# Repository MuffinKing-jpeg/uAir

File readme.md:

# uAir

Small air monitor with OLED screen

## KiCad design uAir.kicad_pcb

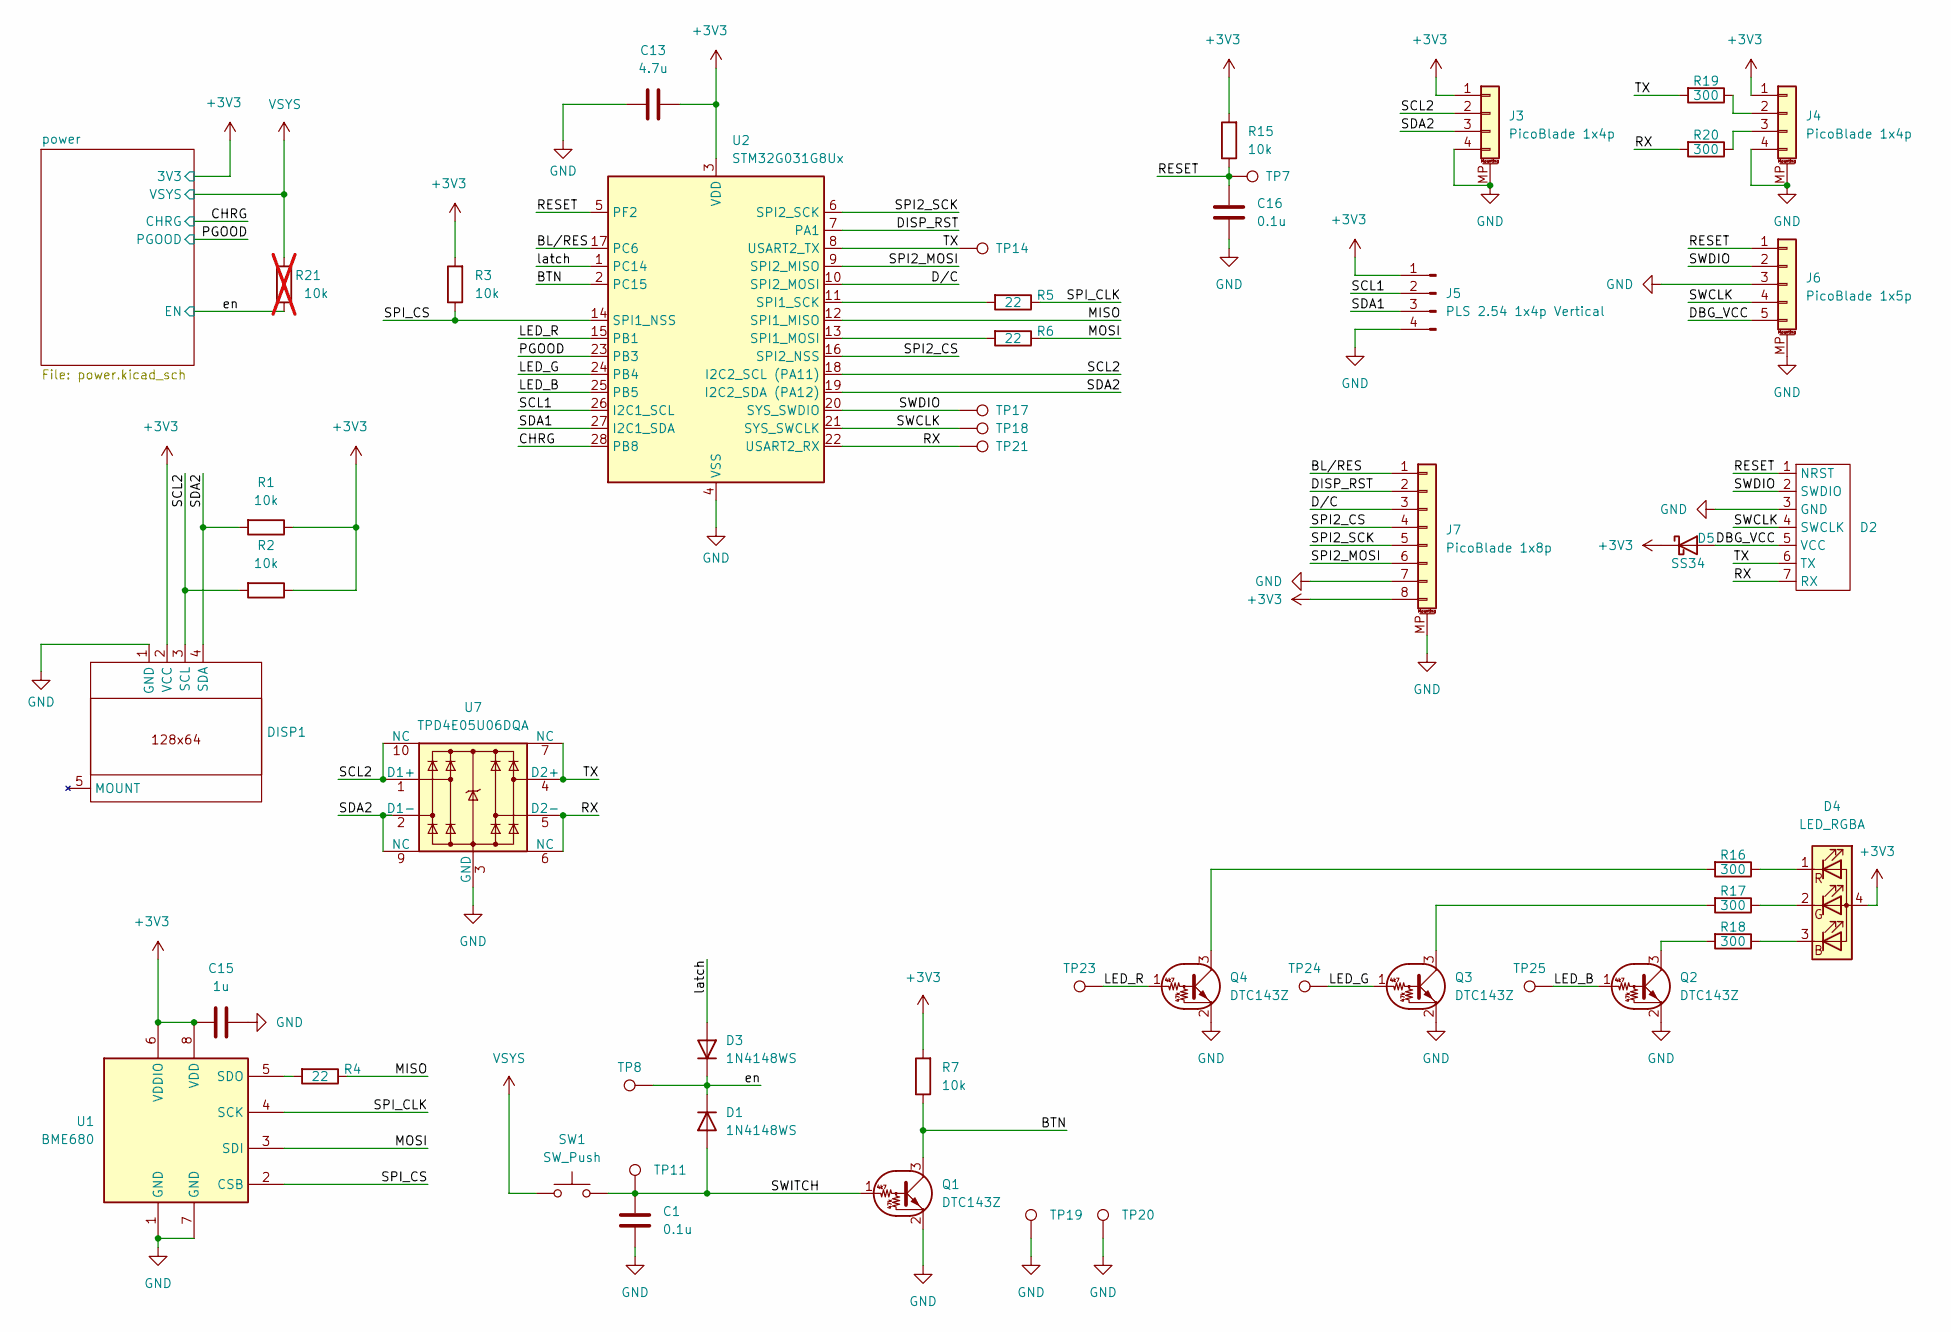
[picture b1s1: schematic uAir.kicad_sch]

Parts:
C1, C16: 0.1u; C_0402_1005Metric
C13: 4.7u; C_0603_1608Metric
C15: 1u; C_0603_1608Metric
D1, D3: 1N4148WS; D_SOD-323; LCSC C6423741
D2: DBG-CLIP-7_pad
D4: LED_RGBA; LED_LiteOn_LTST-C19HE1WT; LCSC C125110
D5: SS34; D_SMA
DISP1: OLED_Module_I2C_WeAct
J3, J4: PicoBlade 1x4p; Molex_PicoBlade_53261-0471_1x04-1MP_P1.25mm_Horizontal
J5: PLS 2.54 1x4p Vertical; PinHeader_1x04_P2.54mm_Vertical
J6: PicoBlade 1x5p; Molex_PicoBlade_53261-0571_1x05-1MP_P1.25mm_Horizontal
J7: PicoBlade 1x8p; Molex_PicoBlade_53261-0871_1x08-1MP_P1.25mm_Horizontal
Q1: DTC143Z; SOT-523; LCSC C2828442
Q2, Q3, Q4: DTC143Z; SC-59; LCSC C2828442
R1, R2, R3, R7, R15: 10k; R_0603_1608Metric
R4, R5, R6: 22; R_0603_1608Metric
R16, R17, R18, R19, R20: 300; R_0603_1608Metric
R21: 10k; R_0603_1608Metric; not fitted
SW1: SW_Push; SW_Kailh_Choc_V1V2_Led
TP7: nRESET; TestPoint_THTPad_D1.0mm_Drill0.5mm
TP8: EN; TestPoint_THTPad_D1.0mm_Drill0.5mm
TP11: SWITCH; TestPoint_Pad_D1.0mm
TP14: TX; TestPoint_THTPad_D1.0mm_Drill0.5mm
TP17: SWDIO; TestPoint_THTPad_D1.0mm_Drill0.5mm
TP18: SWCLK; TestPoint_THTPad_D1.0mm_Drill0.5mm
TP19, TP20: GND; TestPoint_THTPad_D1.0mm_Drill0.5mm
TP21: RX; TestPoint_THTPad_D1.0mm_Drill0.5mm
TP23: LED_R; TestPoint_THTPad_D1.0mm_Drill0.5mm
TP24: LED_G; TestPoint_THTPad_D1.0mm_Drill0.5mm
TP25: LED_B; TestPoint_THTPad_D1.0mm_Drill0.5mm
U1: BME680; Bosch_LGA-8_3x3mm_P0.8mm_ClockwisePinNumbering
U2: STM32G031G8Ux; QFN-28_4x4mm_P0.5mm
U7: TPD4E05U06DQA; USON-10_2.5x1.0mm_P0.5mm

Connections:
+3V3: C13.2, C15.1, D4.4 (A), D5.1 (K), DISP1.2 (VCC), J3.1, J4.1, J5.1, J7.8, R1.1, R2.1, R3.2, R7.2, R15.2, U1.6 (VDDIO), U1.8 (VDD), U2.3 (VDD); also elsewhere on the board
/BL/RES: J7.1, U2.17 (PC6)
/BTN: Q1.3 (C), R7.1, U2.2 (PC15)
/CHRG: U2.28 (PB8); also elsewhere on the board
/DBG_VCC: D2.5 (VCC), D5.2 (A), J6.5
/DISP_RST: J7.2, U2.7 (PA1)
/D/C: J7.3, U2.10 (SPI2_MOSI)
/LED_B: Q2.1 (B), TP25.1 (1_1), U2.25 (PB5)
/LED_G: Q3.1 (B), TP24.1 (1_1), U2.24 (PB4)
/LED_R: Q4.1 (B), TP23.1 (1_1), U2.15 (PB1)
/MISO: R4.1, U2.12 (SPI1_MISO)
/MOSI: R6.1, U1.3 (SDI)
/PGOOD: U2.23 (PB3); also elsewhere on the board
/RESET: C16.1, D2.1 (NRST), J6.1, R15.1, TP7.1 (1_1), U2.5 (PF2)
/RX: D2.7 (RX), R20.2, TP21.1 (1_1), U2.22 (USART2_RX), U7.5 (D2-), U7.6 (NC)
/SCL1: J5.2, U2.26 (I2C1_SCL)
/SCL2: DISP1.3 (SCL), J3.2, R2.2, U2.18 (I2C2_SCL (PA11)), U7.1 (D1+), U7.10 (NC)
/SDA1: J5.3, U2.27 (I2C1_SDA)
/SDA2: DISP1.4 (SDA), J3.3, R1.2, U2.19 (I2C2_SDA (PA12)), U7.2 (D1-), U7.9 (NC)
/SPI2_CS: J7.4, U2.16 (SPI2_NSS)
/SPI2_MOSI: J7.6, U2.9 (SPI2_MISO)
/SPI2_SCK: J7.5, U2.6 (SPI2_SCK)
/SPI_CLK: R5.1, U1.4 (SCK)
/SPI_CS: R3.1, U1.2 (CSB), U2.14 (SPI1_NSS)
/SWCLK: D2.4 (SWCLK), J6.4, TP18.1 (1_1), U2.21 (SYS_SWCLK)
/SWDIO: D2.2 (SWDIO), J6.2, TP17.1 (1_1), U2.20 (SYS_SWDIO)
/SWITCH: C1.1, D1.2 (A), Q1.1 (B), SW1.2, TP11.1 (1_1)
/TX: D2.6 (TX), R19.2, TP14.1 (1_1), U2.8 (USART2_TX), U7.4 (D2+), U7.7 (NC)
/en: D1.1 (K), D3.1 (K), R21.1, TP8.1 (1_1); also elsewhere on the board
/latch: D3.2 (A), U2.1 (PC14)
GND: C1.2, C13.1, C15.2, C16.2, D2.3 (GND), DISP1.1 (GND), J3.4, J3.MP (MountPin), J4.4, J4.MP (MountPin), J5.4, J6.3, J6.MP (MountPin), J7.7, J7.MP (MountPin), Q1.2 (E), Q2.2 (E), Q3.2 (E), Q4.2 (E), TP19.1 (1_1), TP20.1 (1_1), U1.1 (GND), U1.7 (GND), U2.4 (VSS), U7.3 (GND), U7.8 (GND); also elsewhere on the board
unnamed: D4.3 (BK), R18.1
unnamed: D4.2 (GK), R17.1
unnamed: D4.1 (RK), R16.1
unnamed: J4.2, R19.1
unnamed: J4.3, R20.1
unnamed: Q2.3 (C), R18.2
unnamed: Q3.3 (C), R17.2
unnamed: Q4.3 (C), R16.2
unnamed: R4.2, U1.5 (SDO)
unnamed: R5.2, U2.11 (SPI1_SCK)
unnamed: R6.2, U2.13 (SPI1_MOSI)
VSYS: R21.2, SW1.1; also elsewhere on the board

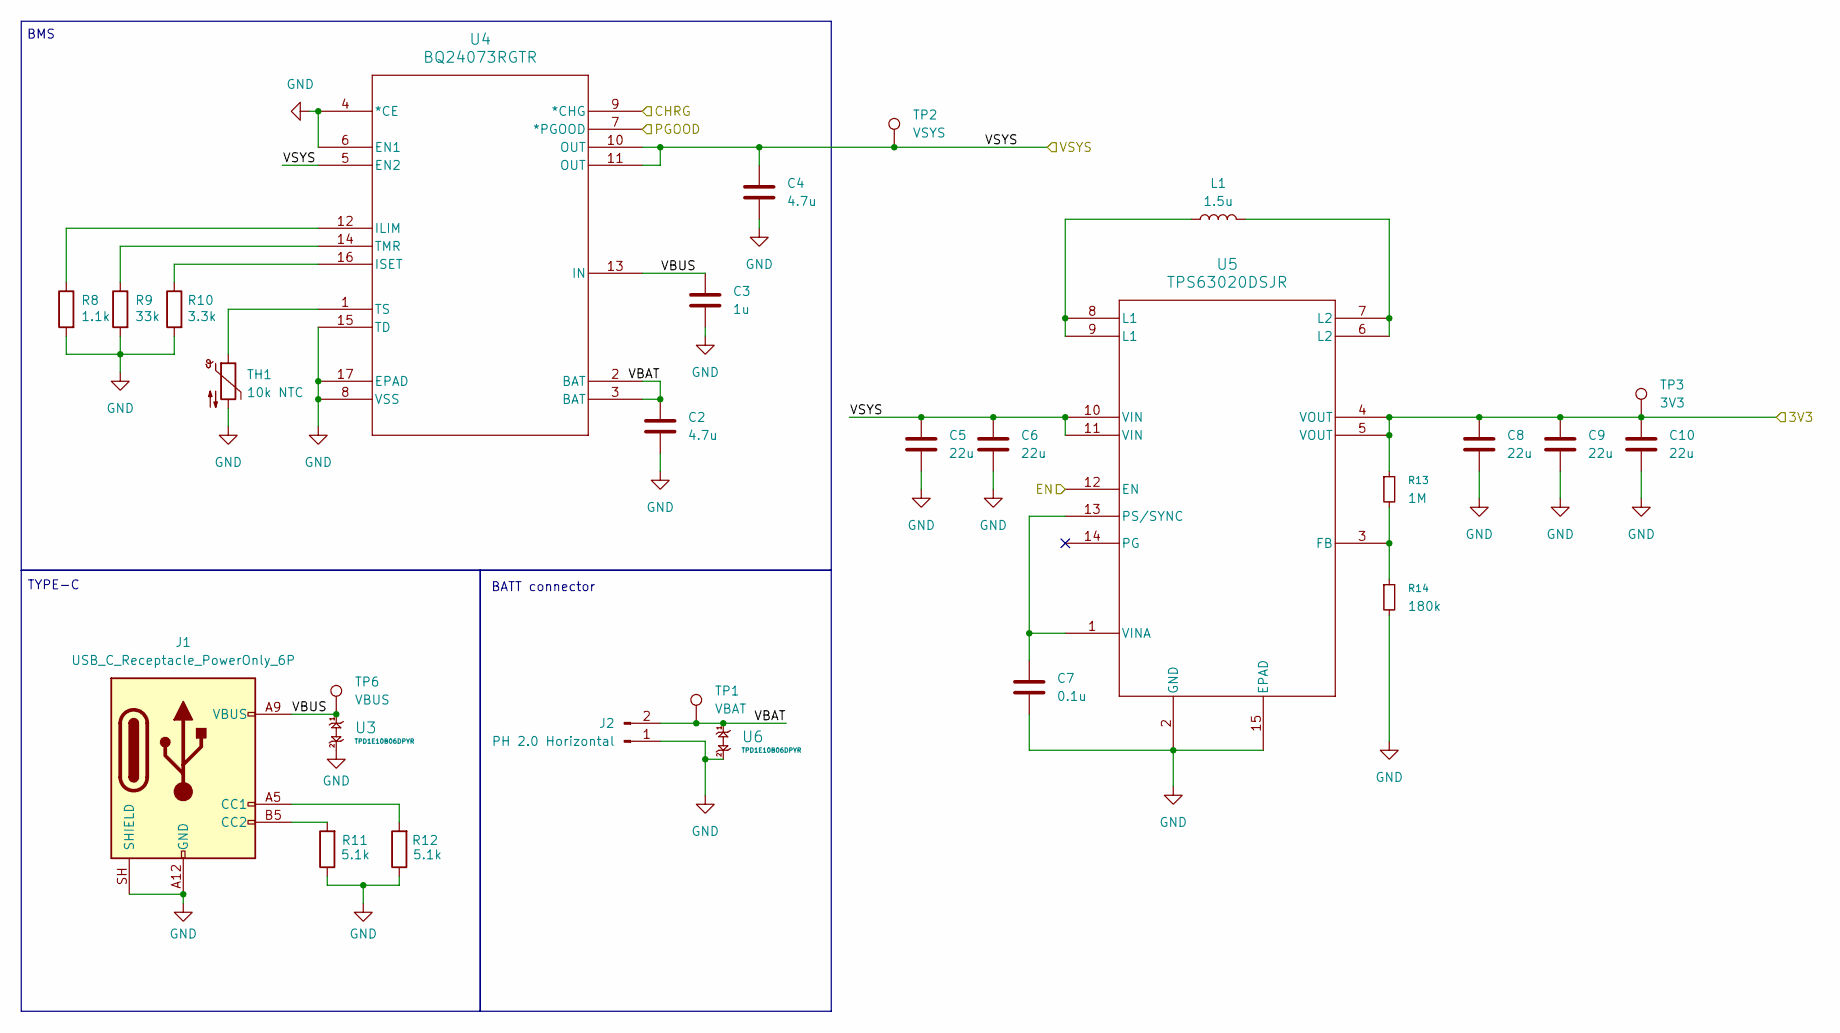
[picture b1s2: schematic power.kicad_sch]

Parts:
C2, C4: 4.7u; C_0603_1608Metric
C3: 1u; C_0603_1608Metric
C5, C6, C8, C9, C10: 22u; C_0805_2012Metric
C7: 0.1u; C_0402_1005Metric
J1: USB_C_Receptacle_PowerOnly_6P; USB_C_Receptacle_GCT_USB4125-xx-x-0190_6P_TopMnt_Horizontal
J2: PH 2.0 Horizontal; JST_PH_S2B-PH-K_1x02_P2.00mm_Horizontal
L1: 1.5u; L_1210_3225Metric
R8: 1.1k; R_0603_1608Metric
R9: 33k; R_0603_1608Metric
R10: 3.3k; R_0603_1608Metric
R11, R12: 5.1k; R_0603_1608Metric
R13: 1M; R_0402_1005Metric
R14: 180k; R_0402_1005Metric
TH1: 10k NTC; R_0402_1005Metric
TP1: VBAT; TestPoint_Pad_D1.0mm
TP2: VSYS; TestPoint_Pad_D1.0mm
TP3: 3V3; TestPoint_Pad_D1.0mm
TP6: VBUS; TestPoint_Pad_D1.0mm
U3, U6: TPD1E10B06DPYR; X1SON-2_L1.0-W0.6-P0.65-BI; LCSC C48260
U4: BQ24073RGTR; RGT16; LCSC C15220
U5: TPS63020DSJR; DSJ14_2P85X1P58; LCSC C15483

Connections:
+3V3: C8.1, C9.1, C10.1, R13.1, TP3.1 (1_1), U5.4 (VOUT), U5.5 (VOUT); also elsewhere on the board
/CHRG: U4.9 (*CHG); also elsewhere on the board
/PGOOD: U4.7 (*PGOOD); also elsewhere on the board
/en: U5.12 (EN); also elsewhere on the board
/power/VBAT: C2.1, J2.2, TP1.1 (1_1), U4.2 (BAT), U4.3 (BAT), U6.1
/power/VBUS: C3.1, J1.A9 (VBUS), J1.B9 (VBUS), TP6.1 (1_1), U3.1, U4.13 (IN)
GND: C2.2, C3.2, C4.2, C5.2, C6.2, C7.2, C8.2, C9.2, C10.2, J1.A12 (GND), J1.B12 (GND), J1.SH (SHIELD), J2.1, R8.2, R9.2, R10.2, R11.1, R12.1, R14.2, TH1.2, U3.2, U4.4 (*CE), U4.6 (EN1), U4.8 (VSS), U4.15 (TD), U4.17 (EPAD), U5.2 (GND), U5.15 (EPAD), U6.2; also elsewhere on the board
unnamed: J1.A5 (CC1), R12.2
unnamed: J1.B5 (CC2), R11.2
unnamed: L1.1, U5.8 (L1), U5.9 (L1)
unnamed: L1.2, U5.6 (L2), U5.7 (L2)
unnamed: R8.1, U4.12 (ILIM)
unnamed: R10.1, U4.16 (ISET)
unnamed: R9.1, U4.14 (TMR)
unnamed: TH1.1, U4.1 (TS)
unnamed: R13.2, R14.1, U5.3 (FB)
unnamed: C7.1, U5.1 (VINA), U5.13 (PS/SYNC)
VSYS: C4.1, C5.1, C6.1, TP2.1 (1_1), U4.5 (EN2), U4.10 (OUT), U4.11 (OUT), U5.10 (VIN), U5.11 (VIN); also elsewhere on the board

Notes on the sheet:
BATT connector
BMS
TYPE-C

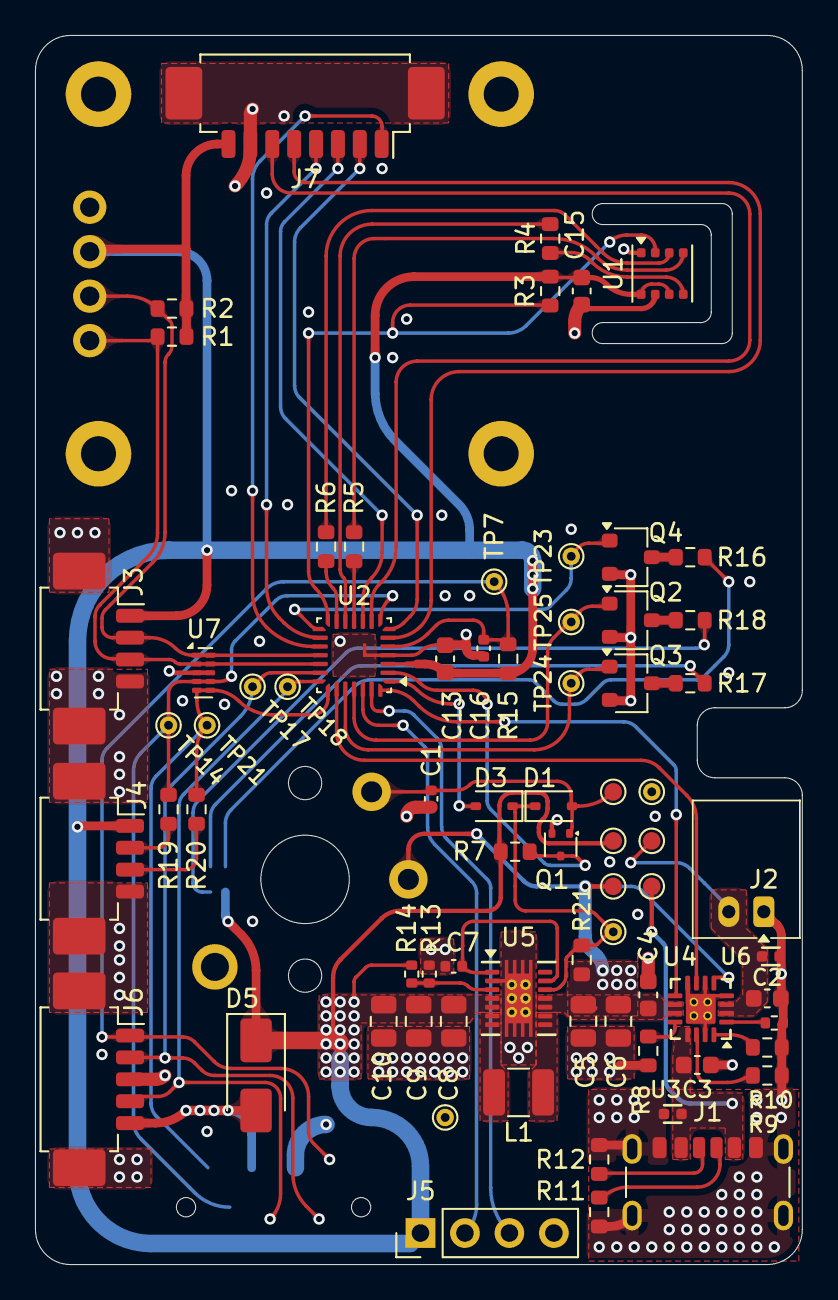
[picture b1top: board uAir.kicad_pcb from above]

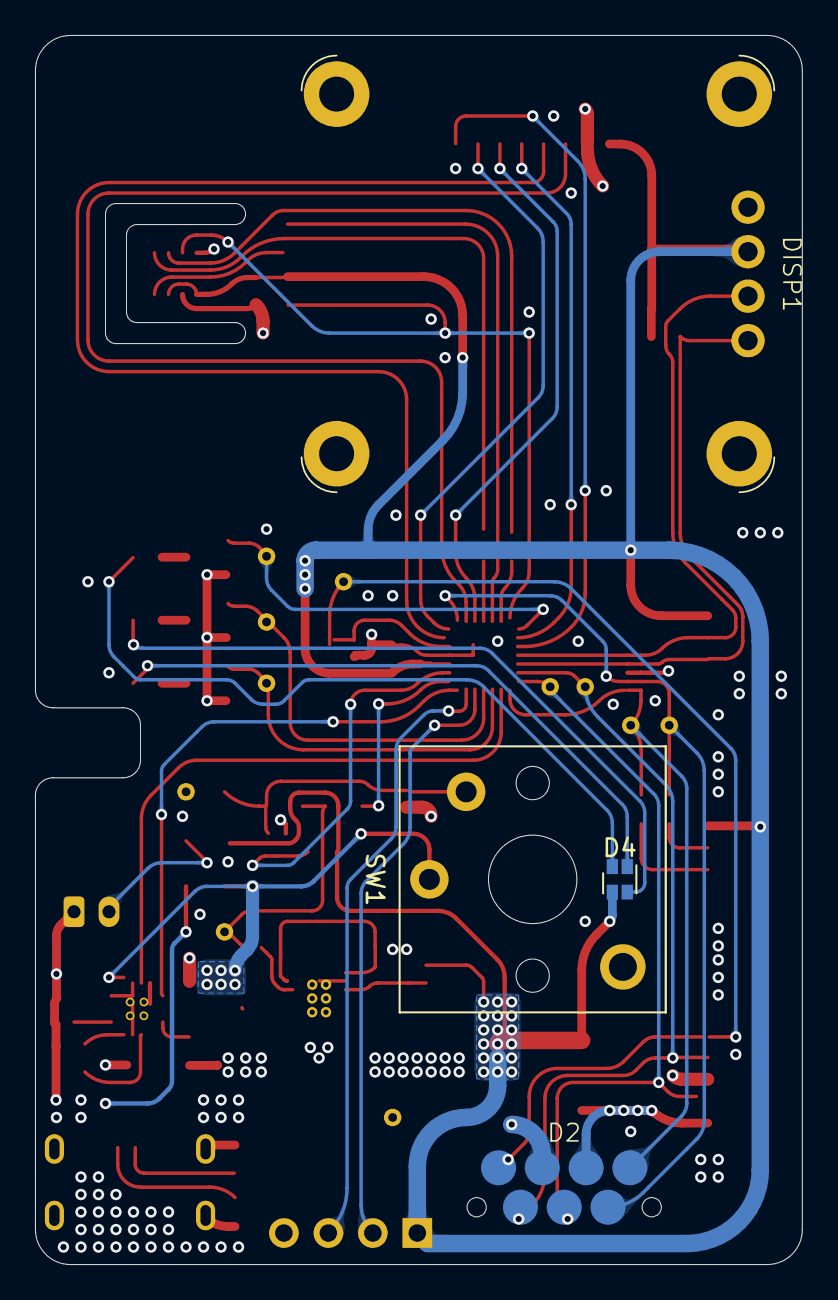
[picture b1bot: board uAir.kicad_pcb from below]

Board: 4 copper layers, 43.8 x 70.2 mm, 77 parts (4 on the bottom side), 55 nets.

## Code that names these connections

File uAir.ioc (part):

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Mcu.Name=STM32G031G(4-6-8)Ux
Mcu.Package=UFQFPN28
Mcu.UserName=STM32G031G8Ux
PA0.Mode=Simplex_Bidirectional_Master
PA0.Signal=SPI2_SCK
PA1.GPIOParameters=GPIO_Label
PA1.GPIO_Label=DISP_RST
PA1.Signal=GPIO_Output
PA11\ [PA9].Mode=I2C
PA11\ [PA9].Signal=I2C2_SCL
PA12\ [PA10].Mode=I2C
PA12\ [PA10].Signal=I2C2_SDA
PA13.Mode=Serial_Wire
PA13.Signal=SYS_SWDIO
PA14-BOOT0.Mode=Serial_Wire
PA14-BOOT0.Signal=SYS_SWCLK
PA15.Signal=USART2_RX
PA2.Signal=USART2_TX
PA4.Mode=Simplex_Bidirectional_Master
PA4.Signal=SPI2_MOSI
PA5.Mode=Full_Duplex_Master
PA5.Signal=SPI1_SCK
PA6.Mode=Full_Duplex_Master
PA6.Signal=SPI1_MISO
PA7.Mode=Full_Duplex_Master
PA7.Signal=SPI1_MOSI
PA8.Mode=NSS_Signal_Hard_Input
PA8.Signal=SPI2_NSS
PB0.Mode=NSS_Signal_Hard_Input
PB0.Signal=SPI1_NSS
PB1.Signal=S_TIM3_CH4
PB4.Signal=S_TIM3_CH1
PB5.Signal=S_TIM3_CH2
PB6.Mode=I2C
PB6.Signal=I2C1_SCL
PB7.Mode=I2C
PB7.Signal=I2C1_SDA
PC14-OSC32_IN\ (PC14).Mode=HSE-External-Clock-Source
PC14-OSC32_IN\ (PC14).Signal=RCC_OSC_IN
PC15-OSC32_OUT\ (PC15).Mode=OSC enable
PC15-OSC32_OUT\ (PC15).Signal=RCC_OSC_EN
RCC.HSE_VALUE=8000000
RCC.SYSCLKFreq_VALUE=64000000
RCC.SYSCLKSource=RCC_SYSCLKSOURCE_PLLCLK
board=custom

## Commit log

2026-05-02 Init project
2026-05-23 PCB WIP
2026-06-01 Sync
2026-06-02 Finished PCB
